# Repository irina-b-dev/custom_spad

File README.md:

# Custom Single Photon Avalanche Detection system with integrated coincidence logic

## Overview

## BOM

Minimal working

[bom_interactive](./bom/ibom.html)

## BOM in test

### APD
| Name | Link                                                 | Price   | Qty | Description            | Code             | Check |
| ---- | ---------------------------------------------------- | ------- | --- | ---------------------- | ---------------- | ----- |
| APD  | https://ro.mouser.com/ProductDetail/193-MTAPD-06-001 | 37,21 € | 2   | Peak Wavelength: 800nm | 193-MTAPD-06-001 | [x]   |

### Voltage Booster + Filter

|                           |                         |           |                    |       |          |      |     |     |
| ------------------------- | ----------------------- | --------- | ------------------ | ----- | -------- | ---- | --- | --- |
| ---  --- |
| Ref.                      | Mfg.                    | Part No.  | Description        |
| R                        | --                      | --        | resistor           | 100K  |          |      |     |     |
| C3                       | --                      | --        | capacitor          | 1µF   |          |      |     |     |
|YH11068A | | | | booster | |

### Quenching + Comparator

|                           |                         |           |                    |       |          |      |     |     |
| ------------------------- | ----------------------- | --------- | ------------------ | ----- | -------- | ---- | --- | --- |
| ---  --- |                         | For SPAD  |                    |       |          |      |     |     |
|                           |                         |           |                    |       |          |      |     |     |
| Ref.                      | Mfg.                    | Part No.  | Description        |       |          |      |     |     |
| APD                       | --                      | DAPD      | diode              |       |          |      |     |     |
| C1                        | --                      | --        | capacitor          | 33µF  | 2.7V     |      |     |     |
| C2                        | --                      | --        | capacitor          | 1µF   |          |      |     |     |
| C3                        | --                      | --        | capacitor          | 1µF   |          |      |     |     |
| C4                        | --                      | --        | capacitor          | 1µF   |          |      |     |     |
| C5                        | --                      | --        | capacitor          | 100nF |          |      |     |     |
| C6                        | --                      | --        | capacitor          | 10nF  |          |      |     |     |
| C7                        | --                      | --        | capacitor          | 100nF |          |      |     |     |
| C8                        | --                      | --        | capacitor          | 100nF |          |      |     |     |
| Cj                        | --                      | --        | capacitor          | 1pF   | 1KV      |      |     |     |
| Cn                        | --                      | --        | capacitor          | 10nF  |          |      |     |     |
| D1                        | OnSemi                  | 1N5818    | diode              |       |          |      |     |     |
| D2                        | OnSemi                  | 1N5819    | diode              |       |          |      |     |     |
| D3                        | Vishay                  | BAT54     | diode              |       |          |      |     |     |
| D4                        | Rohm                    | BAS21HY   | diode              |       |          |      |     |     |
| D5                        | Rohm                    | BAS21HY   | diode              |       |          |      |     |     |
| L1                        | --                      | --        | inductor           | 33µH  | 1.35A pk |      |     |     |
| M1                        | International Rectifier | IRF7832   | MOSFET             |       |          |      |     |     |
| M2                        | Siliconix               | Si7336ADP | MOSFET             |       |          |      |     |     |
| maboi                     | --                      | --        | resistor           | 1M    |          |      |     |     |
| R1                        | --                      | --        | resistor           | 1M    | 1.00%    | 0.1W |     |     |
| R2                        | --                      | --        | resistor           | 100K  |          |      |     |     |
| R3                        | --                      | --        | resistor           | 49.9K |          |      |     |     |
| R4                        | --                      | --        | resistor           | 6.8K  |          |      |     |     |
| R5                        | --                      | --        | resistor           | 20K   |          |      |     |     |
| R6                        | --                      | --        | resistor           | 300   |          |      |     |     |
| R7                        | --                      | --        | resistor           | 1K    |          |      |     |     |
| R8                        | --                      | --        | resistor           | 1.9K  |          |      |     |     |
| R9                        | --                      | --        | resistor           | 6K    |          |      |     |     |
| R10                       | --                      | --        | resistor           | 500K  |          |      |     |     |
| R11                       | --                      | --        | resistor           | 1K    |          |      |     |     |
| R13                       | --                      | --        | resistor           | 150K  |          |      |     |     |
| Rbias                     | --                      | --        | resistor           | 14K   |          |      |     |     |
| Rbias1                    | --                      | --        | resistor           | 10K   |          |      |     |     |
| Rdivider                  | --                      | --        | resistor           | 140K  |          |      |     |     |
| Rdrain                    | --                      | --        | resistor           | 90K   |          |      |     |     |
| Re0                       | --                      | --        | resistor           | 10    |          |      |     |     |
| Ri                        | --                      | --        | resistor           | 200K  |          |      |     |     |
| Rth                       | --                      | --        | resistor           | 1M    |          |      |     |     |
| U1                        | Analog Devices          | LT1172    | integrated circuit |       |          |      |     |     |
| U2                        | Analog Devices          | LT1711    | integrated circuit |       |          |      |     |     |
| U3                        | Analog Devices          | AD8605    | integrated circuit |       |          |      |     |     |
|                           |                         |           |                    |       |          |      |     |     |
| RP_Pico                        |           | Rasberry Pi Pico    |  MCU |       |          |      |     |     |
|                           |                         |           |                    |       |          |      |     |     |

## PIO snippet for detection

```asm

.program detect_pulse

; Assumes:
; - Pin 2 - 4,5 = pulse input
; - Pin  0 - 2,3 = gate/control pin
; - pin base in C must include both

start:
    wait 1 pin 2           ; Wait for rising edge on pulse input
    ;wait 1 pin 0
    jmp pin do_push                       ;jmp pin do_push     ; 
    jmp do_push     ;jmp start              ; Otherwise, skip

do_push:
    in x, 32               ; 
    push block
    jmp start
```

### Note
This project is part of a [bigger project](https://github.com/irina-b-dev/custom-qkd-source)

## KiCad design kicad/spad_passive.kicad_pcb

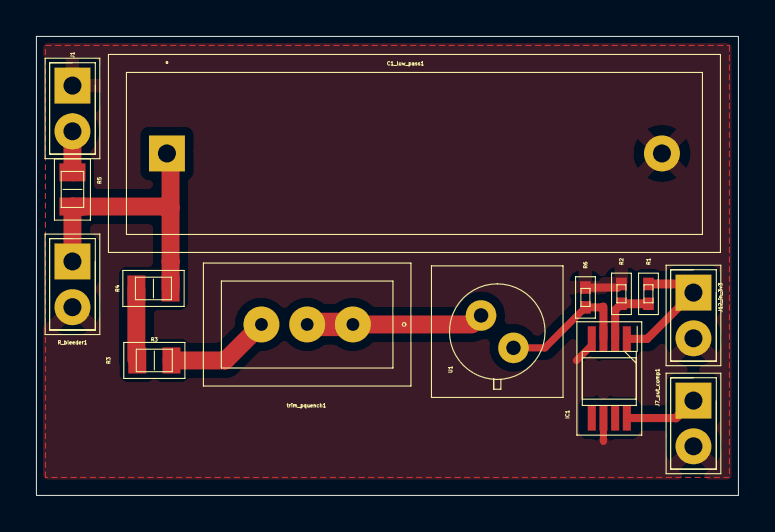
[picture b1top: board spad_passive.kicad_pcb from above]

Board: 2 copper layers, 39.0 x 25.5 mm, 14 parts (0 on the bottom side), 10 nets.

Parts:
C1_low_pass1: MKP1847510254K2
IC1: LT1711IMS8#PBF; SOP65P490X110-8N
J1, J7_out_comp1, J12_in_3v3: 02-0600-20; HDRV2W56P0X254_1X2_508X254X571P
R1, R2, R6: CRT0402-BY-4992GLF; RESC1005X35N
R3, R4, R5: TNPW08051M00BEEN; RESC2012X55N
R_bleeder1: 02-0600-20; HDRV2W56P0X254_1X2_508X254X571P
U1: MTAPD-06-013; MTAPD06013
trim_pquench1: 3296W-1-204LF; 3296W1503LF

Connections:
+3.3V: IC1.1 (V+), J12_in_3v3.1, R1.2
+132V: J1.2, R5.1
GND: C1_low_pass1.2, IC1.4 (V-), IC1.6 (GND), J1.1, J7_out_comp1.2, J12_in_3v3.2, R2.2, R6.2, R_bleeder1.2
unnamed: C1_low_pass1.1, R4.1, R5.2, R_bleeder1.1
unnamed: IC1.2 (+IN), R1.1, R2.1
unnamed: IC1.3 (-IN), R6.1, U1.2 (APD+)
unnamed: IC1.8 (~Q), J7_out_comp1.1
unnamed: R3.1, R4.2
unnamed: R3.2, trim_pquench1.3
unnamed: U1.1 (APD-), trim_pquench1.1, trim_pquench1.2

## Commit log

2026-04-09 Add GNU General Public License version 2
2026-04-09 added the readme
2026-04-09 add initial presentation
2026-06-30 added kicad files
